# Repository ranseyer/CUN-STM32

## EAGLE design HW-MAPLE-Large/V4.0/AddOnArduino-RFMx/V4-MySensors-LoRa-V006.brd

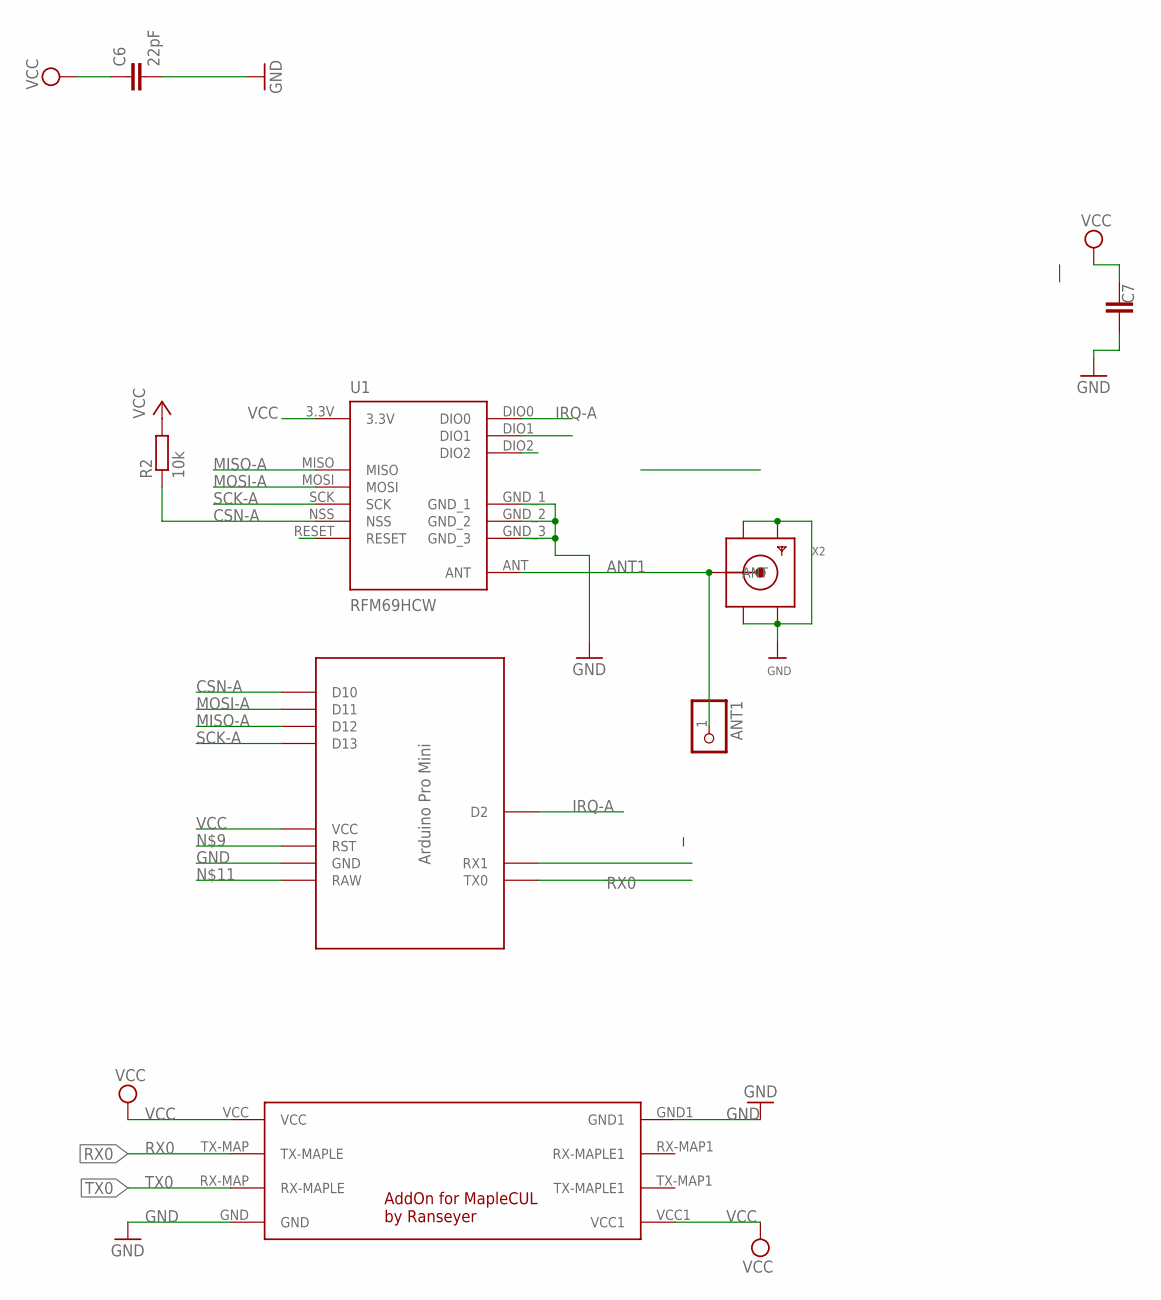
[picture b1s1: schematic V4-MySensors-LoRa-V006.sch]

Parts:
ANT1: PINHD-1X1; 1X01
C6: 22pF; C0805
C7: C-EUC1812; C1812
R2: 10k; M0805
U1: RFM69HCW; RFM69HCW-XXXS2
U$1: MARTIN-PROMINI-SPI; MARTIN-PRO-SPI
U$2: MAPLE-CUL-ADDON-V01; MAPLE-CUL-V01
X2: SMACONNECTOR_EDGE; SMA_EDGELAUNCH

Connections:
ANT1: ANT1.1, U1.ANT, X2.P (ANT)
CSN-A: R2.1, U1.NSS, U$1.D10
GND: C6.2, C7.1, U1.GND_1, U1.GND_2, U1.GND_3, U$1.GND, U$2.GND, U$2.GND1, X2.GND@1 (GND4), X2.GND@2 (GND3), X2.GND@3 (GND2), X2.GND@4 (GND1)
IRQ-A: U1.DIO0, U$1.D2
MISO-A: U1.MISO, U$1.D12
MOSI-A: U1.MOSI, U$1.D11
RX0: U$1.TX0, U$2.TX-MAP (TX-MAPLE)
SCK-A: U1.SCK, U$1.D13
TX0: U$1.RX1, U$2.RX-MAP (RX-MAPLE)
VCC: C6.1, C7.2, R2.2, U1.3.3V, U$1.VCC, U$2.VCC, U$2.VCC1

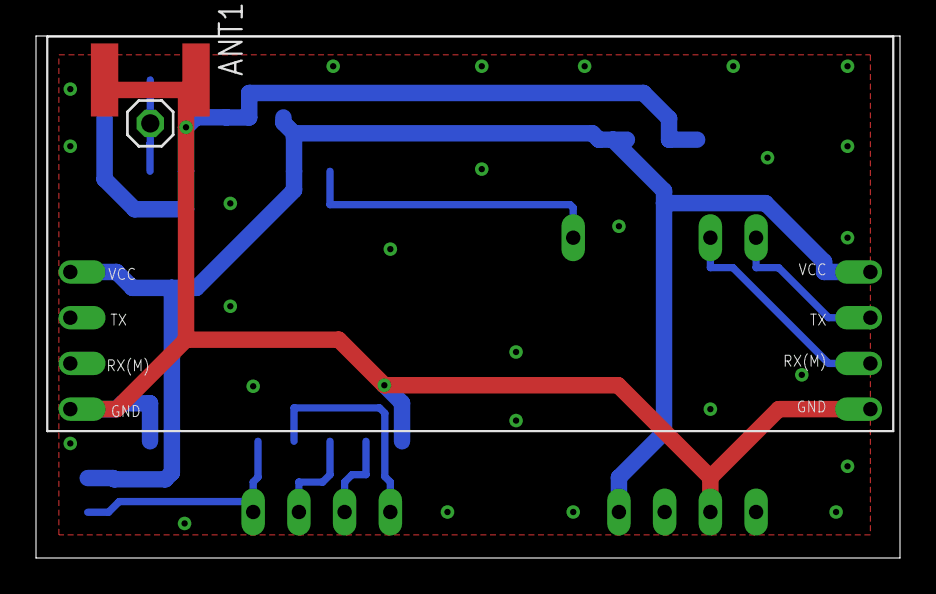
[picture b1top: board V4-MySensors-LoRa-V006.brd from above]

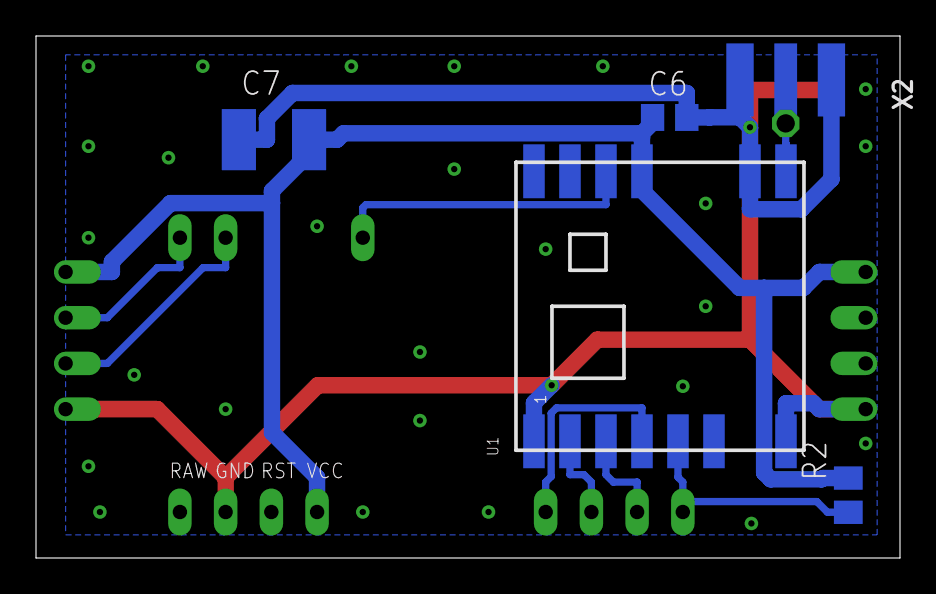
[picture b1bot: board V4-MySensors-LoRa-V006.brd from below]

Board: 2 copper layers, 48.0 x 29.0 mm, 8 parts (5 on the bottom side), 10 nets.

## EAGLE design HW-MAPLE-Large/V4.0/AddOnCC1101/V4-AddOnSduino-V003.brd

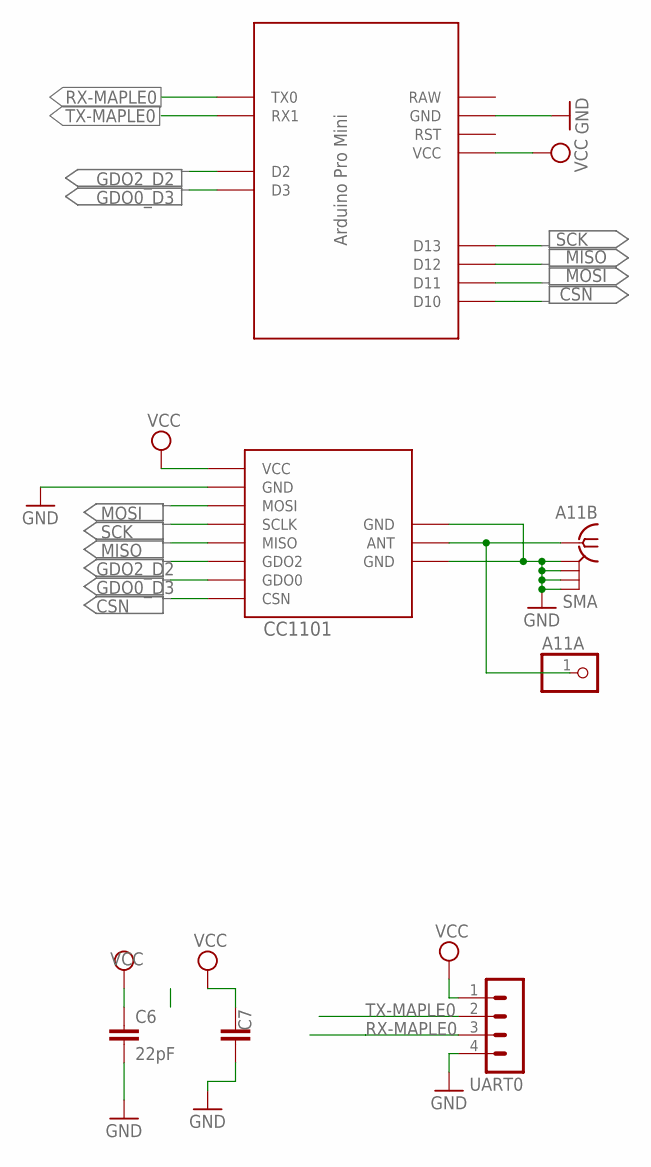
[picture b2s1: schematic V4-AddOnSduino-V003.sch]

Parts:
A11A: PINHD-1X1; 1X01
A11B: SMA
C6: 22pF; C0805
C7: C-EUC1812; C1812
CC1101: CC1101_MODULE1SMD; CC1101_MODULE1_SMD
U$2: MARTIN-PROMINI-CC1101; MARTIN-PRO-CC1101
UART0: MA04-1

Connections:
ANT1: A11A.1, A11B.1, CC1101.ANT
CSN: CC1101.CSN, U$2.D10
GDO0_D3: CC1101.GDO0, U$2.D3
GDO2_D2: CC1101.GDO2, U$2.D2
GND: A11B.GND@1 (2), A11B.GND@2 (3), A11B.GND@3 (4), A11B.GND@4 (5), C6.2, C7.1, CC1101.GND@0 (GND), CC1101.GND@1 (GND), CC1101.GND@2 (GND), U$2.GND, UART0.4
MISO: CC1101.MISO, U$2.D12
MOSI: CC1101.MOSI, U$2.D11
RX-MAPLE0: U$2.TX0, UART0.3
SCK: CC1101.SCLK, U$2.D13
TX-MAPLE0: U$2.RX1, UART0.2
VCC: C6.1, C7.2, CC1101.VCC, U$2.VCC, UART0.1

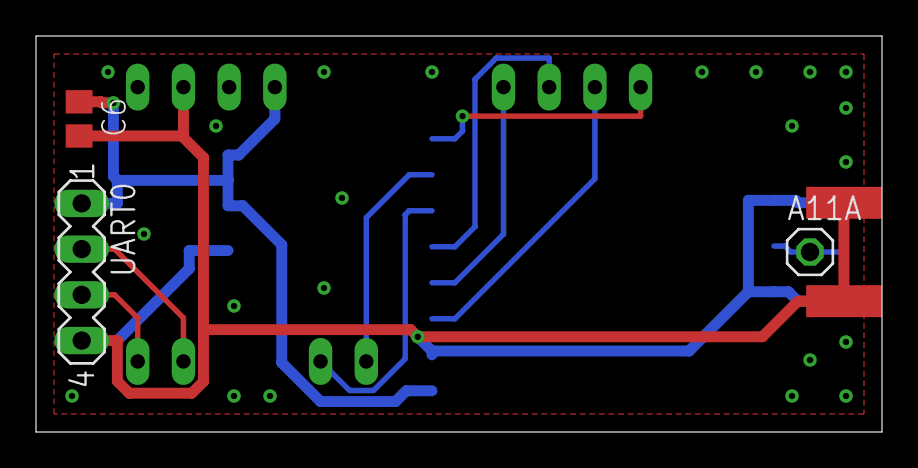
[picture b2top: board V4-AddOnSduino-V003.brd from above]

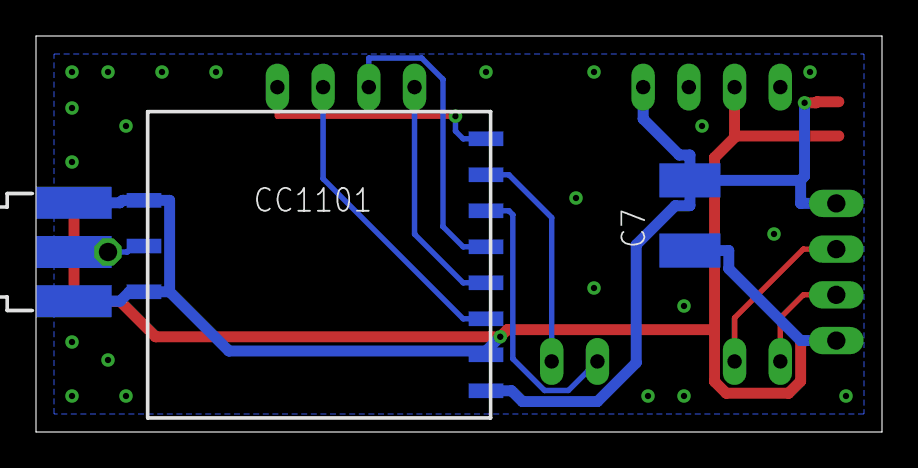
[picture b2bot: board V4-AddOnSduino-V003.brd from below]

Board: 2 copper layers, 47.0 x 22.0 mm, 7 parts (3 on the bottom side), 11 nets.

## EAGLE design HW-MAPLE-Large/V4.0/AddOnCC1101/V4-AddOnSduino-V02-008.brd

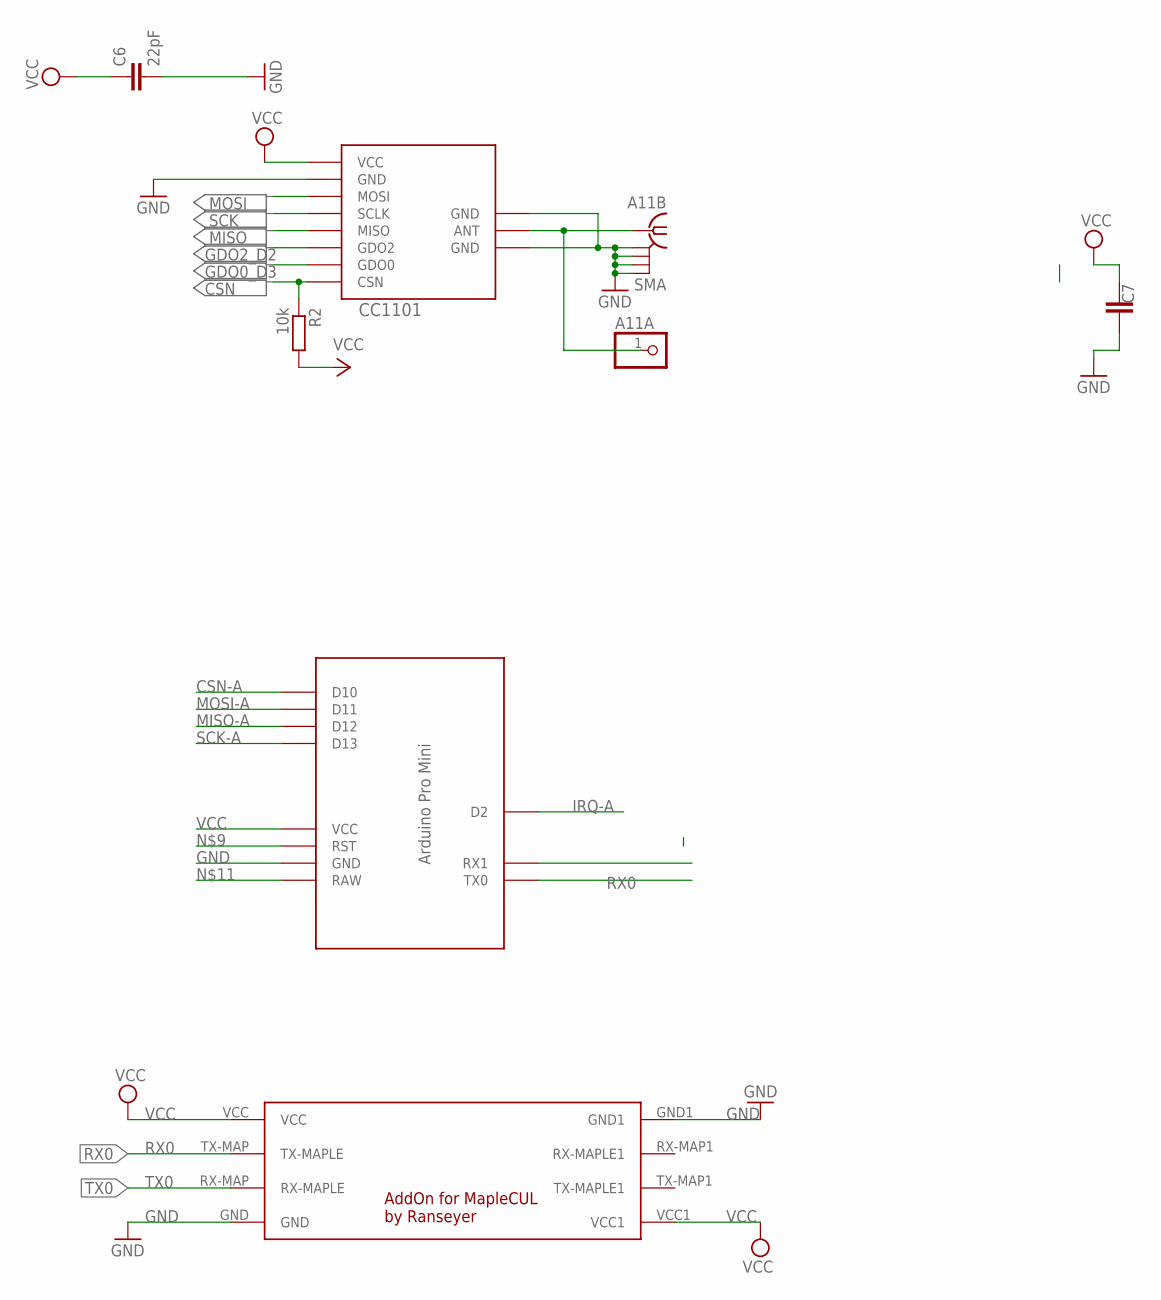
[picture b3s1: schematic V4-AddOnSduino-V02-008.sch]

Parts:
A11A: PINHD-1X1; 1X01
A11B: SMA
C6: 22pF; C0805
C7: C-EUC1812; C1812
CC1101: CC1101_MODULE1SMD; CC1101_MODULE1_SMD
R2: 10k; M0805
U$1: MARTIN-PROMINI-SPI; MARTIN-PRO-SPI
U$2: MAPLE-CUL-ADDON-V01; MAPLE-CUL-V01

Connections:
ANT2: A11A.1, A11B.1, CC1101.ANT
CSN: CC1101.CSN, R2.1
CSN-A: U$1.D10
GDO0_D3: CC1101.GDO0
GDO2_D2: CC1101.GDO2
GND: A11B.GND@1 (2), A11B.GND@2 (3), A11B.GND@3 (4), A11B.GND@4 (5), C6.2, C7.1, CC1101.GND@0 (GND), CC1101.GND@1 (GND), CC1101.GND@2 (GND), U$1.GND, U$2.GND, U$2.GND1
IRQ-A: U$1.D2
MISO: CC1101.MISO
MISO-A: U$1.D12
MOSI: CC1101.MOSI
MOSI-A: U$1.D11
RX0: U$1.TX0, U$2.TX-MAP (TX-MAPLE)
SCK: CC1101.SCLK
SCK-A: U$1.D13
TX0: U$1.RX1, U$2.RX-MAP (RX-MAPLE)
VCC: C6.1, C7.2, CC1101.VCC, R2.2, U$1.VCC, U$2.VCC, U$2.VCC1

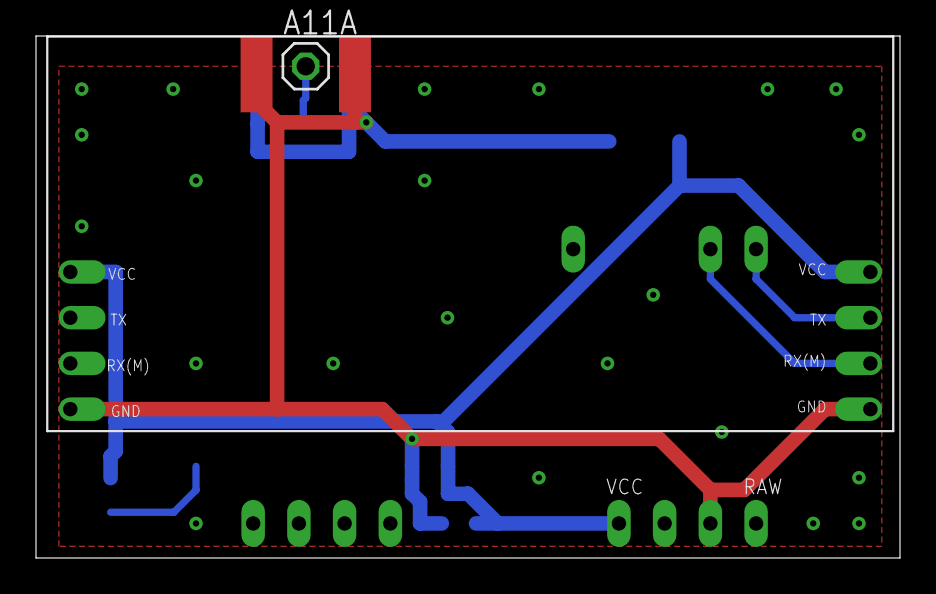
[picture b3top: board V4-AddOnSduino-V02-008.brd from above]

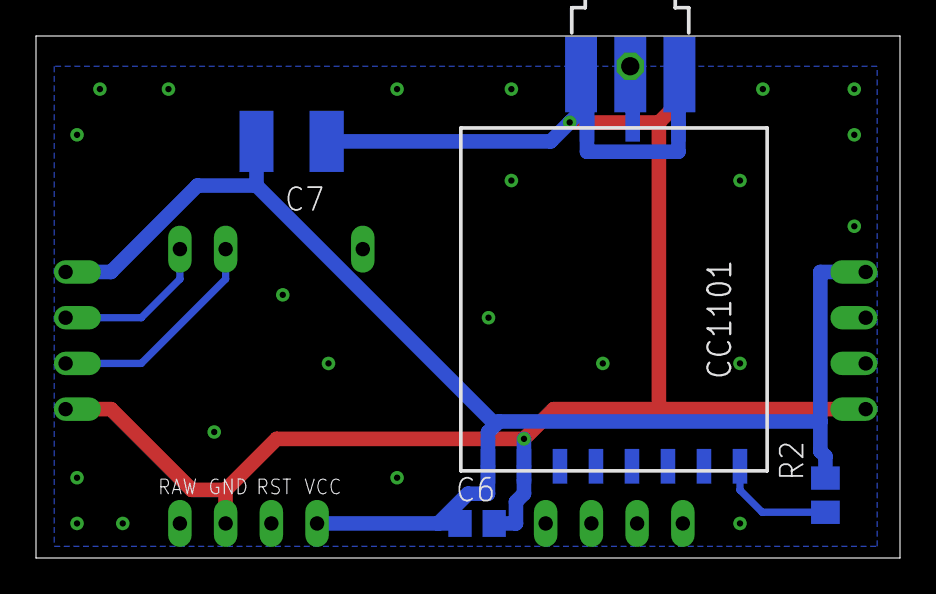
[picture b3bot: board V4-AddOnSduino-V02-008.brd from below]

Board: 2 copper layers, 48.0 x 29.0 mm, 8 parts (5 on the bottom side), 6 nets.

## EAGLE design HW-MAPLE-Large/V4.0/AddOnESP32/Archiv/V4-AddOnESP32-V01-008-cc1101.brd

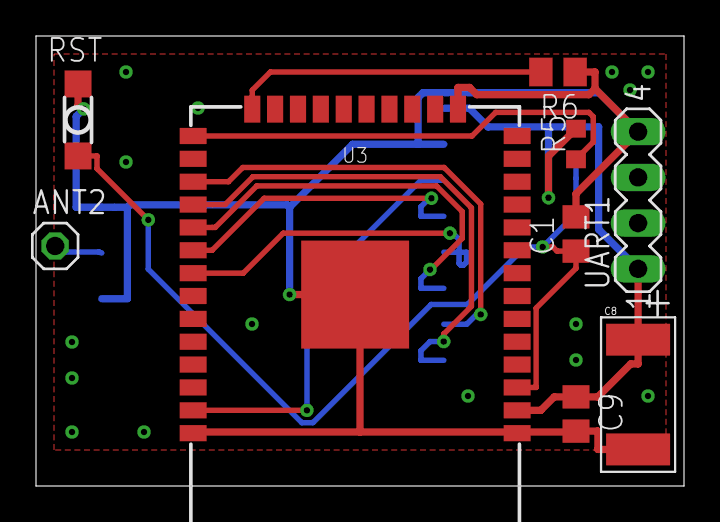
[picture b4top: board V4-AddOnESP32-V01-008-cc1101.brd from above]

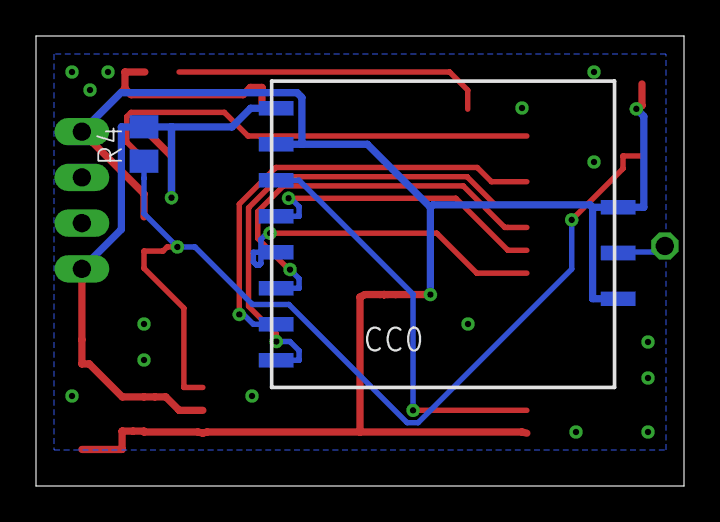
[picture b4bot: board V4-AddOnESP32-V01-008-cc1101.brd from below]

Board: 2 copper layers, 36.0 x 25.0 mm, 11 parts (2 on the bottom side), 12 nets.

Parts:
ANT2: 1X01
C1: 2u2; C0805
C8: 330u; VISHAY_C
C9: 22u; C0805
CC0: CC1101; CC1101_MODULE1_SMD
R4: 10k; M0805
R5: 10k; R0603
R6: 10K; M0805
RST: DTSM-3
U3: ESP-WROOM-32
UART1: MA04-1

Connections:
ANT0: ANT2.1, CC0.ANT
EN: C1.1, R4.1, RST.2, U3.3
GND: C1.2, C8.-, C9.2, CC0.GND@0, CC0.GND@1, CC0.GND@2, R6.1, RST.1, U3.1, U3.15, U3.38, U3.GND, UART1.4
IO0: R5.1, U3.25
IO2: R6.2, U3.24
IO5: CC0.GDO2, U3.29
IO16: CC0.GDO0, U3.27
IO17: CC0.CSN, U3.28
IO18: CC0.SCLK, U3.30
IO19: CC0.MISO, U3.31
IO23: CC0.MOSI, U3.37
VCC: C8.+, C9.1, CC0.VCC, R4.2, R5.2, U3.2, UART1.1

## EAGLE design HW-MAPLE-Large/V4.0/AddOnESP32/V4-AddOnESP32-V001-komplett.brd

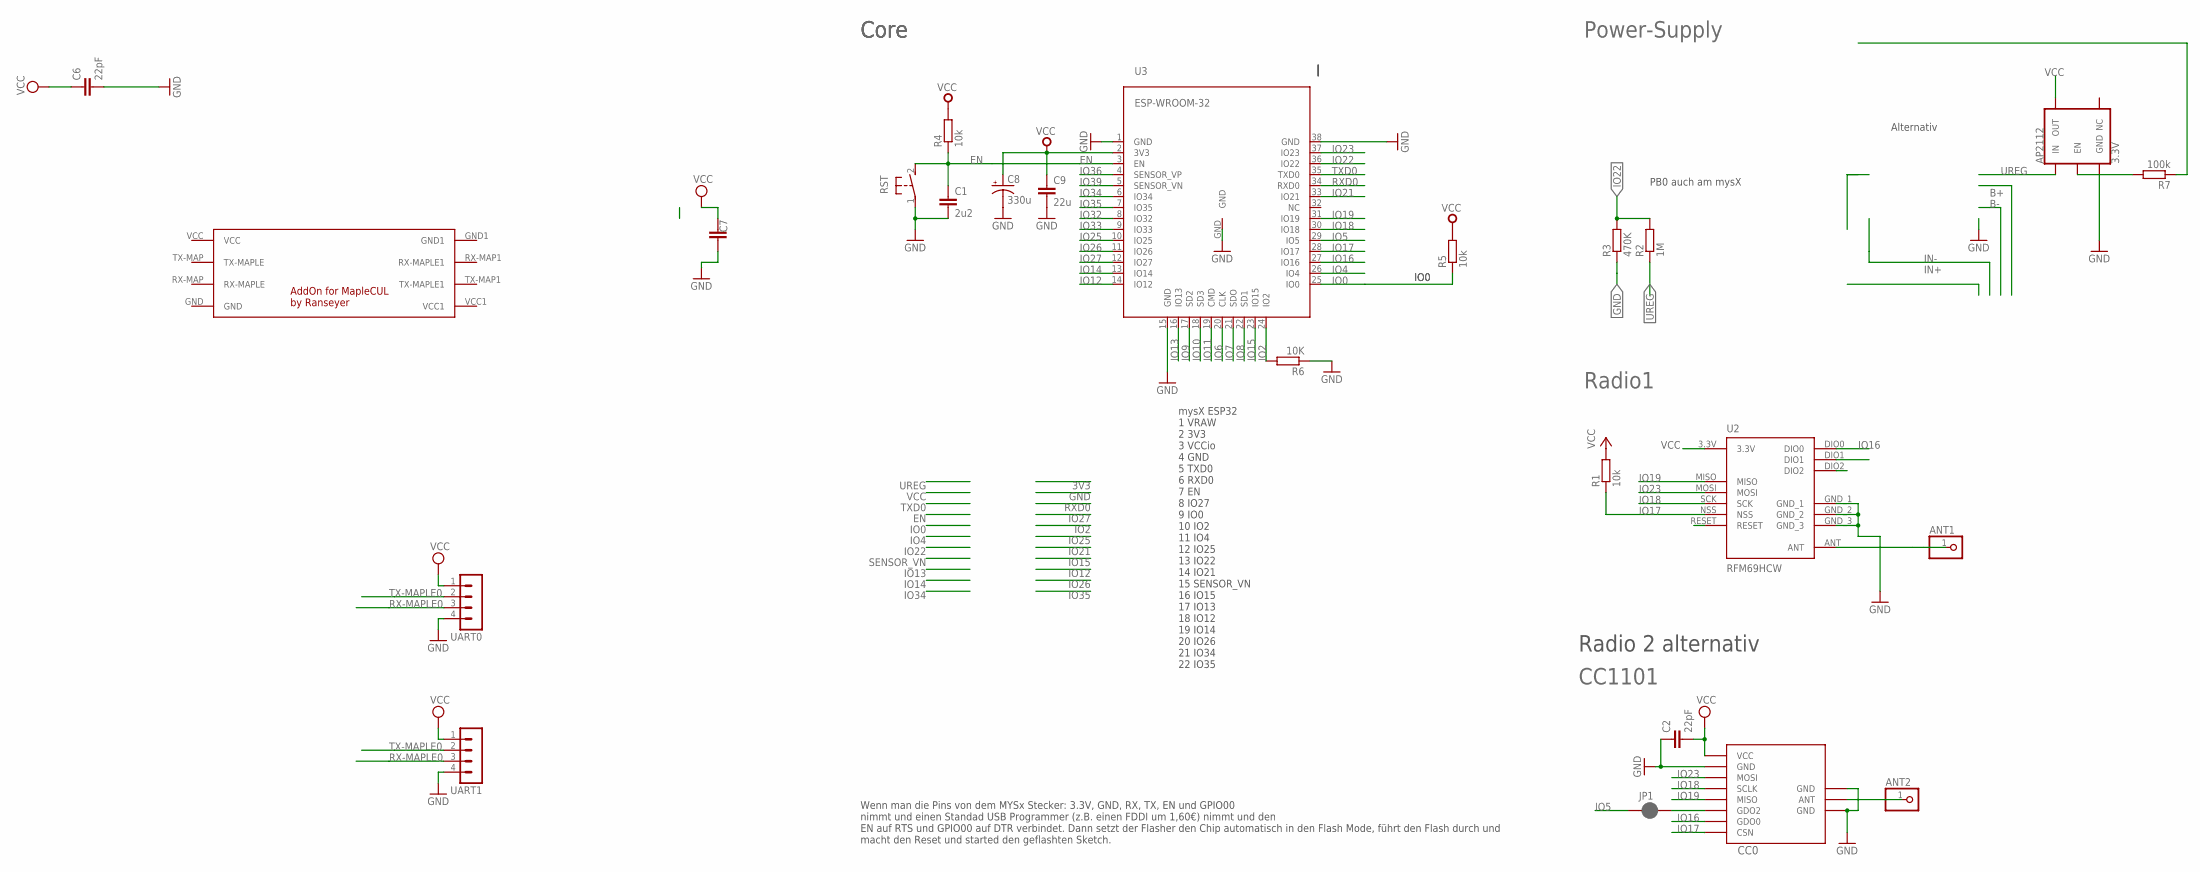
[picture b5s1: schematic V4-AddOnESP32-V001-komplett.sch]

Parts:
ANT1, ANT2: PINHD-1X1; 1X01
AP2112: 3.3V; SOT23-5
C1: 2u2; C0805
C2, C6: 22pF; C0805
C7: C-EUC1812; C1812
C8: 330u; VISHAY_C
C9: 22u; C0805
CC0: CC1101; CC1101_MODULE1_SMD
JP1: JUMPER-SMT_2_NC_PASTE_NO-SILK; SMT-JUMPER_2_NC_PASTE_NO-SILK
R1, R4: 10k; M0805
R2: 1M; M0805
R3: 470K; M0805
R5: 10k; R0603
R6: 10K; M0805
R7: 100k; M0805
RST: DTSM-3
U2: RFM69HCW; RFM69HCW-XXXS2
U3: ESP-WROOM-32
U$1: MAPLE-CUL-ADDON-V01; MAPLE-CUL-V01
UART0, UART1: MA04-1

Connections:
ANT0: ANT2.1, CC0.ANT
ANT1: ANT1.1, U2.ANT
EN: C1.1, R4.1, RST.2, U3.3 (EN)
GND: AP2112.2 (GND), C1.2, C2.1, C6.2, C7.1, C8.-, C9.2, CC0.GND@0 (GND), CC0.GND@1 (GND), CC0.GND@2 (GND), R3.1, R6.1, RST.1, U2.GND_1, U2.GND_2, U2.GND_3, U3.1 (GND), U3.15 (GND), U3.38 (GND), U3.GND, UART0.4, UART1.4
IN++: R7.1
IO0: R5.1, U3.25 (IO0)
IO2: R6.2, U3.24 (IO2)
IO4: U3.26 (IO4)
IO5: JP1.1, U3.29 (IO5)
IO6: U3.20 (CLK)
IO7: U3.21 (SDO)
IO8: U3.22 (SD1)
IO9: U3.17 (SD2)
IO10: U3.18 (SD3)
IO11: U3.19 (CMD)
IO12: U3.14 (IO12)
IO13: U3.16 (IO13)
IO14: U3.13 (IO14)
IO15: U3.23 (IO15)
IO16: CC0.GDO0, U2.DIO0, U3.27 (IO16)
IO17: CC0.CSN, R1.1, U2.NSS, U3.28 (IO17)
IO18: CC0.SCLK, U2.SCK, U3.30 (IO18)
IO19: CC0.MISO, U2.MISO, U3.31 (IO19)
IO21: U3.33 (IO21)
IO22: R2.2, R3.2, U3.36 (IO22)
IO23: CC0.MOSI, U2.MOSI, U3.37 (IO23)
IO25: U3.10 (IO25)
IO26: U3.11 (IO26)
IO27: U3.12 (IO27)
IO32: U3.8 (IO32)
IO33: U3.9 (IO33)
IO34: U3.6 (IO34)
IO35: U3.7 (IO35)
IO36: U3.4 (SENSOR_VP)
IO39: U3.5 (SENSOR_VN)
MAYBE_IO5: CC0.GDO2, JP1.2
unnamed: AP2112.3 (EN), R7.2
RX-MAPLE0: UART0.3, UART1.3
RXD0: U3.34 (RXD0)
TX-MAPLE0: UART0.2, UART1.2
TXD0: U3.35 (TXD0)
UREG: AP2112.1 (IN), R2.1
VCC: AP2112.5 (OUT), C2.2, C6.1, C7.2, C8.+, C9.1, CC0.VCC, R1.2, R4.2, R5.2, U2.3.3V, U3.2 (3V3), UART0.1, UART1.1

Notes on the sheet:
mysX ESP32 1 VRAW 2 3V3 3 VCCio 4 GND 5 TXD0 6 RXD0 7 EN 8 IO27 9 IO0 10 IO2 11 IO4 12 IO25 13 IO22 14 IO21 15 SENSOR_VN 16 IO15 17 IO13 18 IO12 19 IO14 20 IO26 21 IO34 22 IO35
PB0 auch am mysX
Radio1
Radio 2 alternativ
CC1101
Wenn man die Pins von dem MYSx Stecker: 3.3V, GND, RX, TX, EN und GPIO00 nimmt und einen Standad USB Programmer (z.B. einen FDDI um 1,60€) nimmt und den EN auf RTS und GPIO00 auf DTR verbindet. Dann setzt der Flasher den Chip automatisch in den Flash Mode, führt den Flash durch und macht den Reset 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
Alternativ
Core
Power-Supply

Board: 2 copper layers, 24 parts (3 on the bottom side), 19 nets, no tracks yet.

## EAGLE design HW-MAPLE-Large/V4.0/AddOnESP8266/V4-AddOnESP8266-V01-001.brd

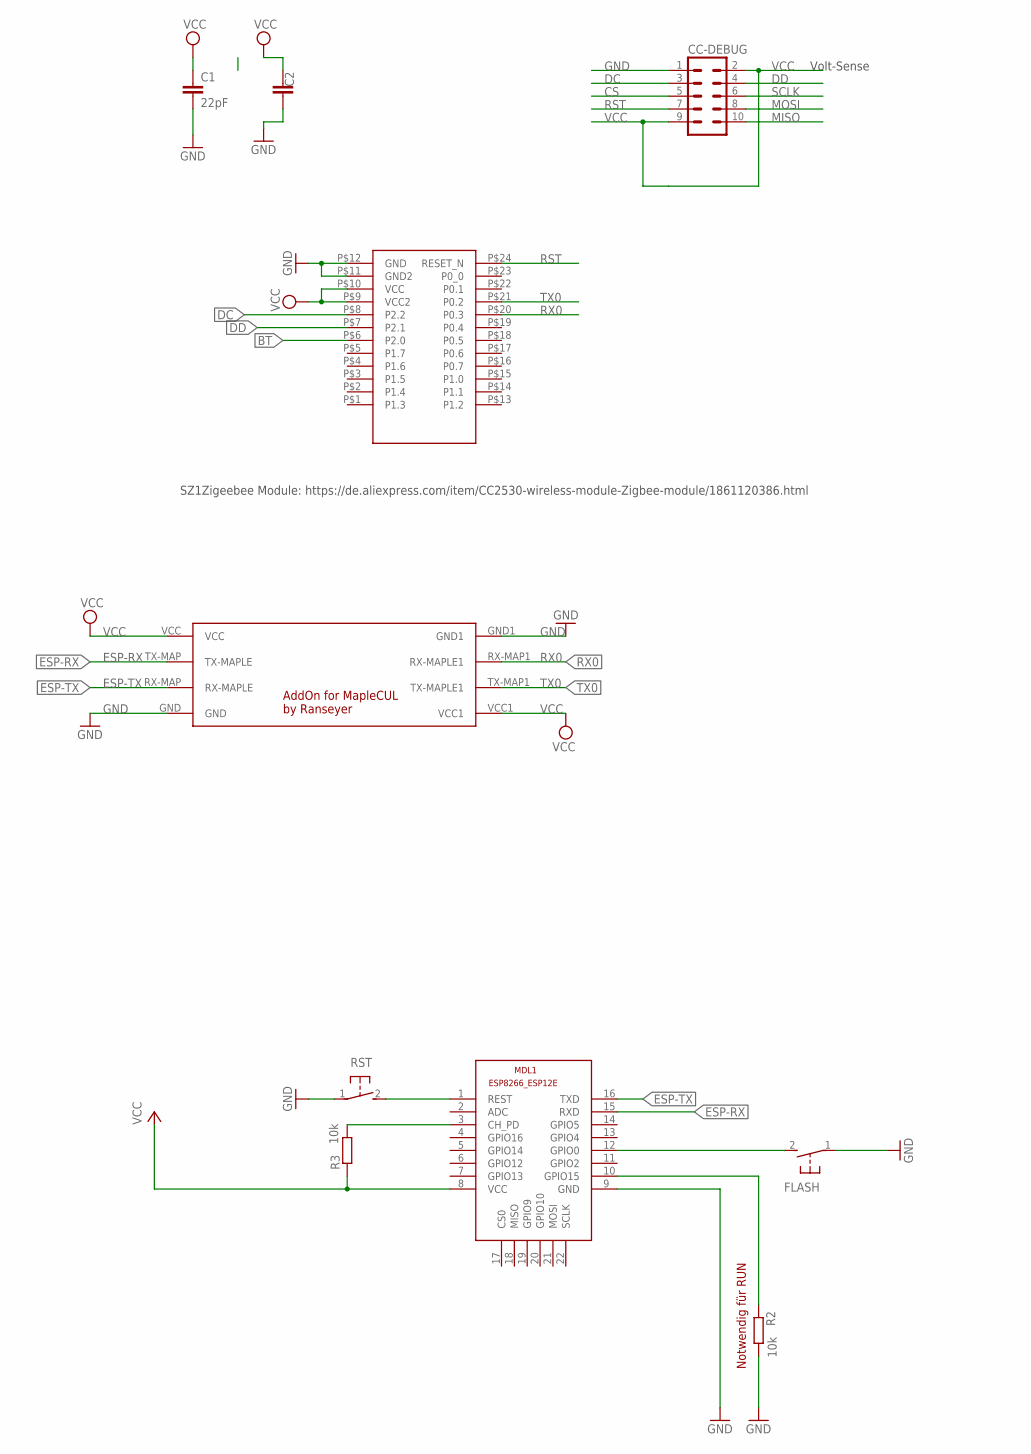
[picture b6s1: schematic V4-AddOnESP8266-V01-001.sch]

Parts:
C1: 22pF; C0805
C2: C-EUC1812; C1812
CC-DEBUG: CONN_05X2SHD_LOCK; 2X5-SHROUDED_LOCK
FLASH: DTSM-3
MDL1: ESP8266-12EESP8266-ESP12E; ESP8266-ESP12E
R2, R3: 10k; M1206
RST: DTSM-3
U$1: MAPLE-CUL-ADDON-V01; MAPLE-CUL-V01
U$2: CC2530; SZ1ZIGBEE-SMD

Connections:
BT: U$2.P$6 (P2.0)
CS: CC-DEBUG.5
DC: CC-DEBUG.3, U$2.P$8 (P2.2)
DD: CC-DEBUG.4, U$2.P$7 (P2.1)
ESP-RX: MDL1.15 (RXD), U$1.TX-MAP (TX-MAPLE)
ESP-TX: MDL1.16 (TXD), U$1.RX-MAP (RX-MAPLE)
GND: C1.2, C2.1, CC-DEBUG.1, FLASH.1, MDL1.9 (GND), R2.2, RST.1, U$1.GND, U$1.GND1, U$2.P$11 (GND2), U$2.P$12 (GND)
MISO: CC-DEBUG.10
MOSI: CC-DEBUG.8
unnamed: MDL1.1 (REST), RST.2
unnamed: FLASH.2, MDL1.12 (GPIO0)
unnamed: MDL1.3 (CH_PD), R3.2
unnamed: MDL1.10 (GPIO15), R2.1
RST: CC-DEBUG.7, U$2.P$24 (RESET_N)
RX0: U$1.RX-MAP1 (RX-MAPLE1), U$2.P$20 (P0.3)
SCLK: CC-DEBUG.6
TX0: U$1.TX-MAP1 (TX-MAPLE1), U$2.P$21 (P0.2)
VCC: C1.1, C2.2, CC-DEBUG.2, CC-DEBUG.9, MDL1.8 (VCC), R3.1, U$1.VCC, U$1.VCC1, U$2.P$9 (VCC2), U$2.P$10 (VCC)

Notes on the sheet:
Volt-Sense
SZ1Zigeebee Module: https://de.aliexpress.com/item/CC2530-wireless-module-Zigbee-module/1861120386.html
Notwendig für RUN

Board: 2 copper layers, 10 parts (4 on the bottom side), 13 nets, no tracks yet.

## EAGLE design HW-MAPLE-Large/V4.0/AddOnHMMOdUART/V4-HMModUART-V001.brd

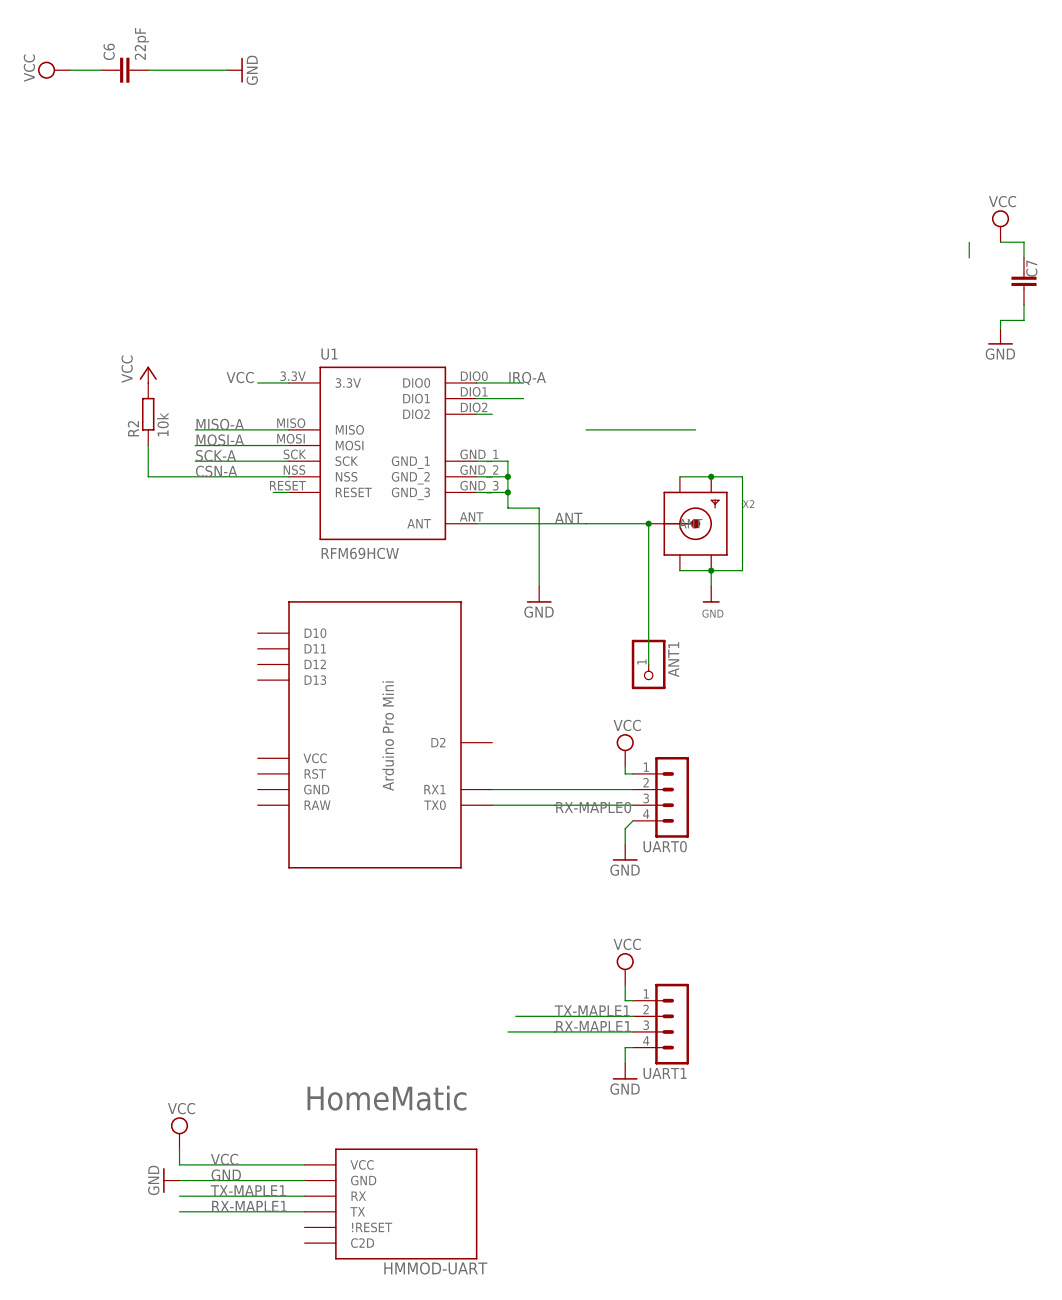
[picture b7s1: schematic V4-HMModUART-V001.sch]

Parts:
ANT1: PINHD-1X1; 1X01
C6: 22pF; C0805
C7: C-EUC1812; C1812
HMMOD-UART: HM-MOD-UARTDIL; HM-MOD-UART-DIL
R2: 10k; M0805
U1: RFM69HCW; RFM69HCW-XXXS2
U$1: MARTIN-PROMINI-SPI; MARTIN-PRO-SPI
UART0, UART1: MA04-1
X2: SMACONNECTOR_EDGE; SMA_EDGELAUNCH

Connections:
ANT: U1.ANT
ANT1: ANT1.1, X2.P (ANT)
CSN-A: R2.1, U1.NSS
GND: C6.2, C7.1, HMMOD-UART.2 (GND), U1.GND_1, U1.GND_2, U1.GND_3, UART0.4, UART1.4, X2.GND@1 (GND4), X2.GND@2 (GND3), X2.GND@3 (GND2), X2.GND@4 (GND1)
IRQ-A: U1.DIO0
MISO-A: U1.MISO
MOSI-A: U1.MOSI
unnamed: U$1.RX1, UART0.2
RX-MAPLE0: U$1.TX0, UART0.3
RX-MAPLE1: HMMOD-UART.5 (TX), UART1.3
SCK-A: U1.SCK
TX-MAPLE1: HMMOD-UART.6 (RX), UART1.2
VCC: C6.1, C7.2, HMMOD-UART.1 (VCC), R2.2, U1.3.3V, UART0.1, UART1.1

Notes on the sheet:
HomeMatic

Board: 2 copper layers, 10 parts (4 on the bottom side), 8 nets, no tracks yet.

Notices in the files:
parts and their libraries:
microbuilder: This work is placed in the public domain, and may be freely used for commercial and non-commercial work with the following conditions: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
SparkFun-Passives: Licensing: Creative Commons ShareAlike 4.0 International - https://creativecommons.org/licenses/by-sa/4.0
